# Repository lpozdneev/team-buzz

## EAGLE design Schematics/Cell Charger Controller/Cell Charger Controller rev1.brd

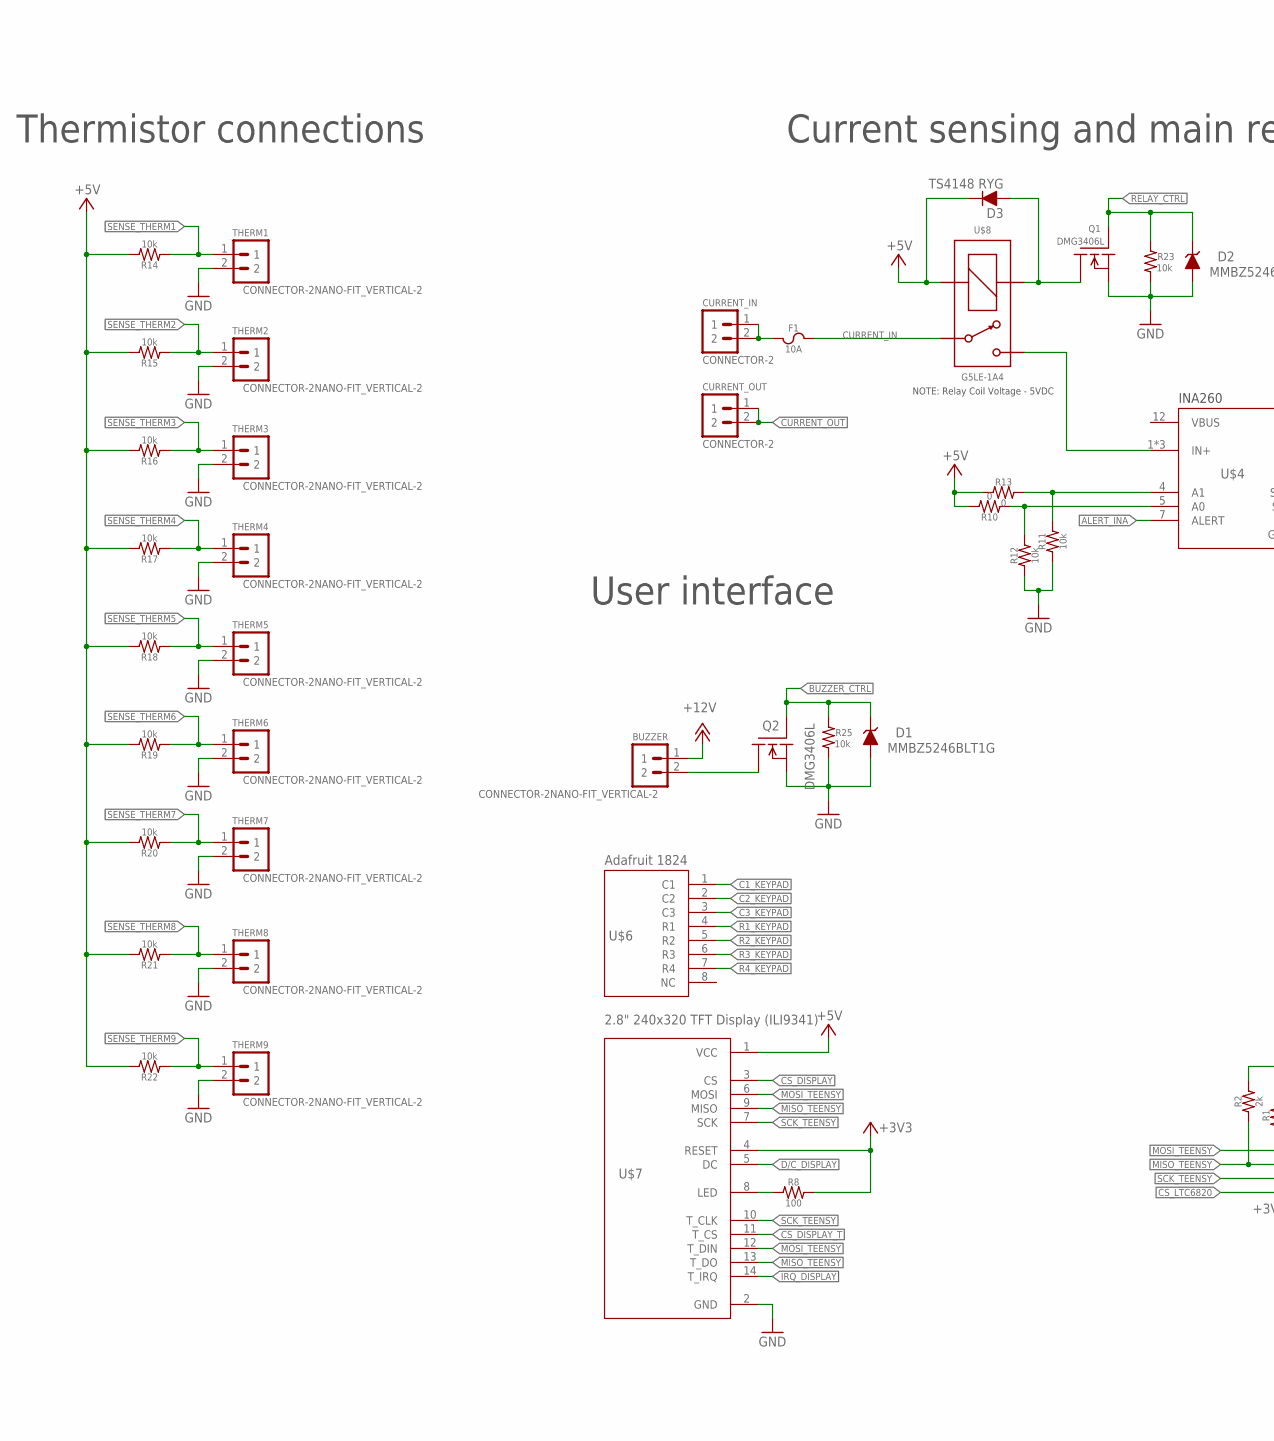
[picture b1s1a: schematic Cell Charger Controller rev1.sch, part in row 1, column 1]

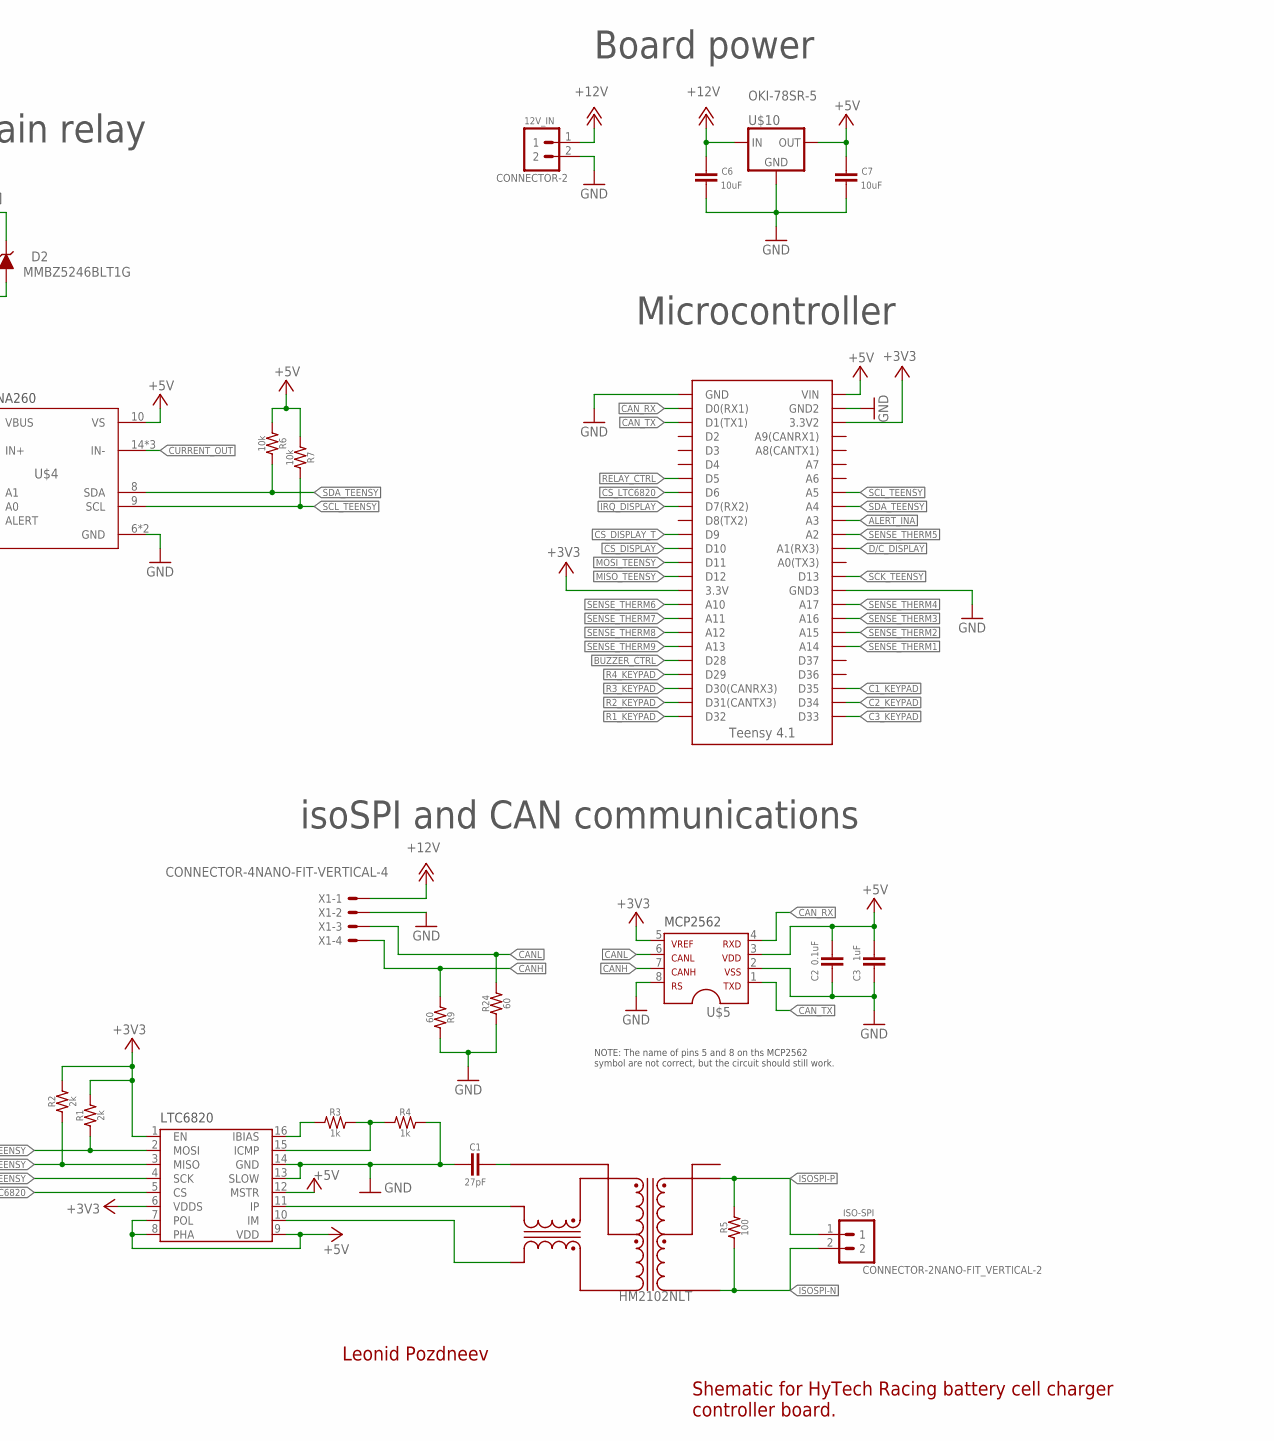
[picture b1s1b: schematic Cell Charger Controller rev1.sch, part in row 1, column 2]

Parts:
12V_IN: CONNECTOR-2; 39288020
BUZZER: CONNECTOR-2NANO-FIT_VERTICAL-2; 1053091202
C1: 27pF; 0603-CAP
C2: 0.1uF; 0603-CAP
C3: 1uF; 0603-CAP
C6, C7: 10uF; 0603-CAP
CURRENT_IN: CONNECTOR-2; 39288020
CURRENT_OUT: CONNECTOR-2; 39288020
D1, D2: MMBZ5246BLT1G; SOT23
D3: TS4148 RYG; 0805_D
F1: 10A; MINI-BLADE_FUSE_HOLDER
ISO-SPI: CONNECTOR-2NANO-FIT_VERTICAL-2; 1053091202
Q1, Q2: DMG3406L; SOT23
R1, R2: 2k; 0603-RES
R3, R4: 1k; 0603-RES
R5, R8: 100; 0603-RES
R6, R7, R11, R12, R14, R15, R16, R17, R18, R19, R20, R21, R22, R23, R25: 10k; 0603-RES
R9, R24: 60; 0603-RES
R10, R13: 0; 0603-RES
THERM1, THERM2, THERM3, THERM4, THERM5, THERM6, THERM7, THERM8, THERM9: CONNECTOR-2NANO-FIT_VERTICAL-2; 1053091202
U1: HM2102NLT
U$2: TEENSY_4.1_SIMPLE
U$3: LTC6820; MSOP-16
U$4: INA260; TSSOP-16
U$5: MCP2562FD; SOIC-08
U$6: ADAFRUIT_1824_KEYPAD
U$7: ILI9341_TOUCH_SCREEN
U$8: G5LE-1A4
U$10: OKI-78SR-5; OKI-78SR
X1: CONNECTOR-4NANO-FIT-VERTICAL-4; 1053101204

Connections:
+3V3: R1.2, R2.2, R8.2, U$2.3.3V, U$2.3.3V2, U$3.1 (EN), U$3.6 (VDDS), U$5.5, U$7.4 (RESET)
+5V: C2.1, C3.1, C7.1, D3.C, R6.1, R7.1, R10.2, R13.1, R14.2, R15.2, R16.2, R17.2, R18.2, R19.2, R20.2, R21.2, R22.2, U$2.VIN, U$3.7 (POL), U$3.8 (PHA), U$3.9 (VDD), U$3.12 (MSTR), U$4.10 (VS), U$5.3, U$7.1 (VCC), U$8.2 (COIL-), U$10.3 (OUT)
+12V: 12V_IN.1, BUZZER.1, C6.1, U$10.1 (IN), X1.1
ALERT_INA: U$2.A3, U$4.7 (ALERT)
BUZZER_CTRL: D1.3 (C), Q2.1 (G), R25.2, U$2.D28
C1_KEYPAD: U$2.D35, U$6.1 (C1)
C2_KEYPAD: U$2.D34, U$6.2 (C2)
C3_KEYPAD: U$2.D33, U$6.3 (C3)
CANH: R9.1, U$5.7, X1.4
CANL: R24.2, U$5.6, X1.3
CAN_RX: U$2.D0(RX1), U$5.4
CAN_TX: U$2.D1(TX1), U$5.1
CS_DISPLAY: U$2.D10, U$7.3 (CS)
CS_DISPLAY_T: U$2.D9, U$7.11 (T_CS)
CS_LTC6820: U$2.D6, U$3.5 (CS)
CURRENT_IN: F1.R1 (2), F1.R2 (2), U$8.P
CURRENT_OUT: CURRENT_OUT.1, CURRENT_OUT.2, U$4.14 (IN-), U$4.15 (IN-), U$4.16 (IN-)
D/C_DISPLAY: U$2.A1(RX3), U$7.5 (DC)
GND: 12V_IN.2, C1.2, C2.2, C3.2, C6.2, C7.2, D1.1 (A), D2.1 (A), Q1.2 (S), Q2.2 (S), R4.2, R9.2, R11.1, R12.1, R23.1, R24.1, R25.1, THERM1.2, THERM2.2, THERM3.2, THERM4.2, THERM5.2, THERM6.2, THERM7.2, THERM8.2, THERM9.2, U$2.GND, U$2.GND2, U$2.GND3, U$3.13 (SLOW), U$3.14 (GND), U$4.6 (GND), U$4.11 (GND), U$5.2, U$5.8, U$7.2 (GND), U$10.2 (GND), X1.2
IRQ_DISPLAY: U$2.D7(RX2), U$7.14 (T_IRQ)
ISOSPI-N: ISO-SPI.2, R5.1, U1.P$3 (MX-)
ISOSPI-P: ISO-SPI.1, R5.2, U1.P$1 (MX+)
MISO_TEENSY: R2.1, U$2.D12, U$3.3 (MISO), U$7.9 (MISO), U$7.13 (T_DO)
MOSI_TEENSY: R1.1, U$2.D11, U$3.2 (MOSI), U$7.6 (MOSI), U$7.12 (T_DIN)
unnamed: C1.1, U1.P$11 (TCT)
unnamed: U1.P$12 (TD+), U$3.11 (IP)
unnamed: U1.P$10 (TD-), U$3.10 (IM)
unnamed: R3.1, U$3.16 (IBIAS)
unnamed: R3.2, R4.1, U$3.15 (ICMP)
unnamed: R11.2, R13.2, U$4.4 (A1)
unnamed: R10.1, R12.2, U$4.5 (A0)
unnamed: R8.1, U$7.8 (LED)
unnamed: CURRENT_IN.1, CURRENT_IN.2, F1.L1 (1), F1.L2 (1)
unnamed: U$4.1 (IN+), U$4.2 (IN+), U$4.3 (IN+), U$8.S
unnamed: D3.A, Q1.3 (D), U$8.1 (COIL+)
unnamed: BUZZER.2, Q2.3 (D)
R1_KEYPAD: U$2.D32, U$6.4 (R1)
R2_KEYPAD: U$2.D31(CANTX) (D31(CANTX3)), U$6.5 (R2)
R3_KEYPAD: U$2.D30(CANRX) (D30(CANRX3)), U$6.6 (R3)
R4_KEYPAD: U$2.D29, U$6.7 (R4)
RELAY_CTRL: D2.3 (C), Q1.1 (G), R23.2, U$2.D5
SCK_TEENSY: U$2.D13, U$3.4 (SCK), U$7.7 (SCK), U$7.10 (T_CLK)
SCL_TEENSY: R7.2, U$2.A5, U$4.9 (SCL)
SDA_TEENSY: R6.2, U$2.A4, U$4.8 (SDA)
SENSE_THERM1: R14.1, THERM1.1, U$2.A14
SENSE_THERM2: R15.1, THERM2.1, U$2.A15
SENSE_THERM3: R16.1, THERM3.1, U$2.A16
SENSE_THERM4: R17.1, THERM4.1, U$2.A17
SENSE_THERM5: R18.1, THERM5.1, U$2.A2
SENSE_THERM6: R19.1, THERM6.1, U$2.A10
SENSE_THERM7: R20.1, THERM7.1, U$2.A11
SENSE_THERM8: R21.1, THERM8.1, U$2.A12
SENSE_THERM9: R22.1, THERM9.1, U$2.A13

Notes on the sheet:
NOTE: The name of pins 5 and 8 on ths MCP2562 symbol are not correct, but the circuit should still work.
INA260
MCP2562
LTC6820
NOTE: Relay Coil Voltage - 5VDC
Leonid Pozdneev
Shematic for HyTech Racing battery cell charger controller board.
User interface
Thermistor connections
Current sensing and main relay
Microcontroller
isoSPI and CAN communications
Board power

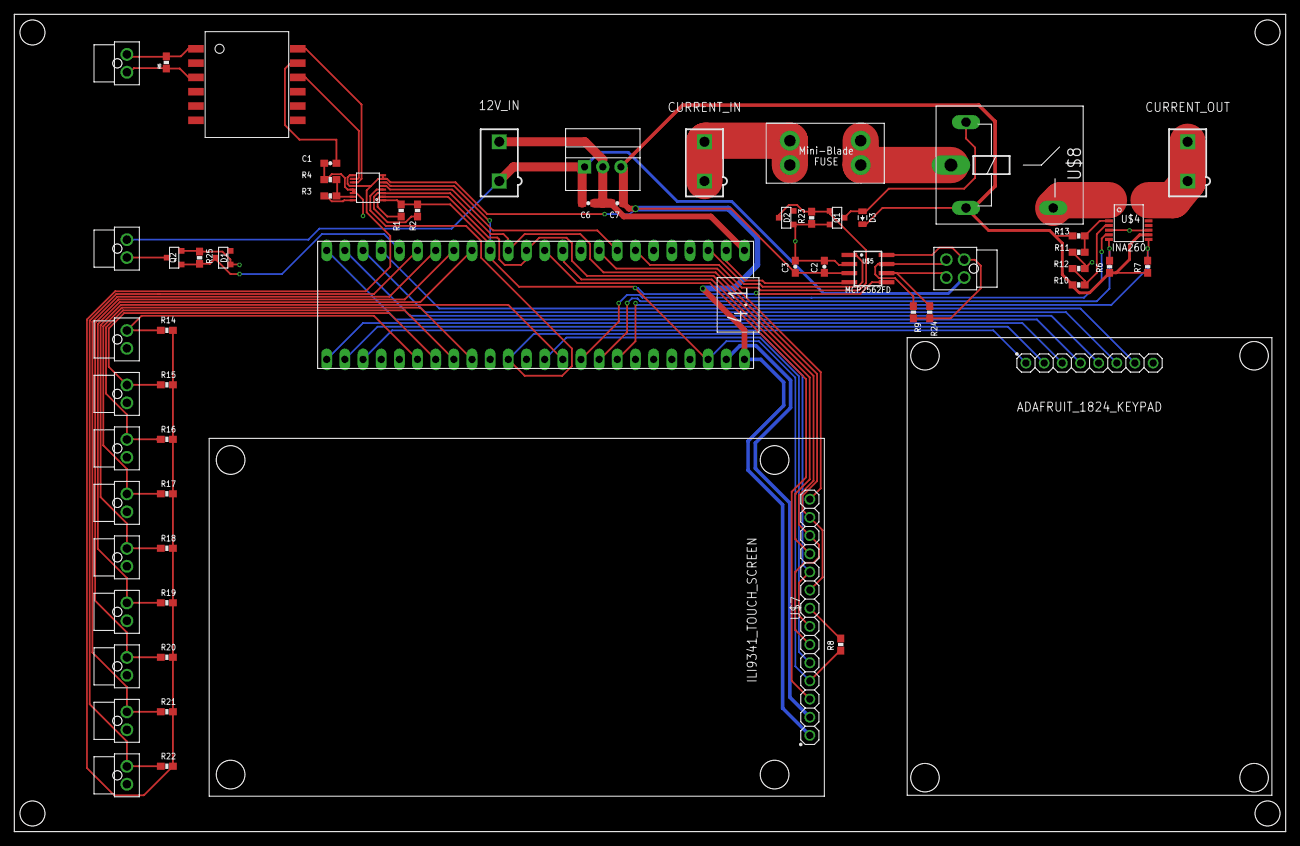
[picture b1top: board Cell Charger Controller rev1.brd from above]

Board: 2 copper layers, 177.8 x 114.3 mm, 60 parts (0 on the bottom side), 53 nets.

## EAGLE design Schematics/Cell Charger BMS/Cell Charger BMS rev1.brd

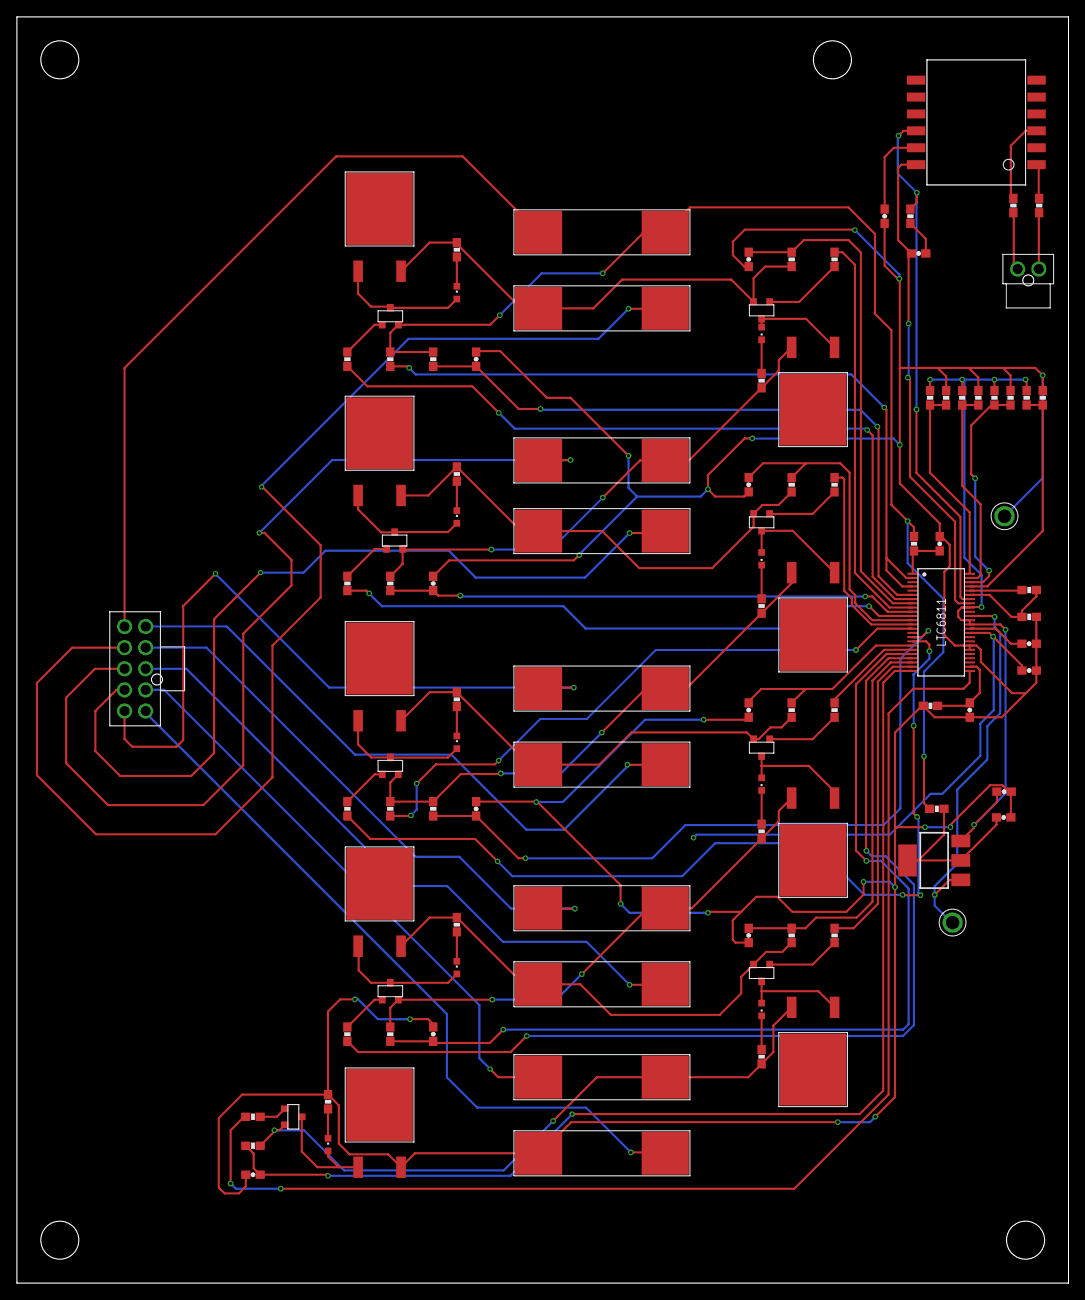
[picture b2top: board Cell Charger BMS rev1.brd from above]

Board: 2 copper layers, 124.5 x 149.9 mm, 110 parts (0 on the bottom side), 88 nets.

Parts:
C1_B, C2_B, C8_B: 1uF; 0603-CAP
C3_B: 15pF; 0603-CAP
C4_B: 10nF; 0603-CAP
C6_B, C7_B: 100nF; 0603-CAP
C_5: 10nF; 0603-CAP
DRAIN1:C, DRAIN2:C, DRAIN3:C, DRAIN4:C, DRAIN5:C, DRAIN6:C, DRAIN7:C, DRAIN8:C, DRAIN9:C: 10nF; 0603-CAP
DRAIN1:DISCHARGE, DRAIN2:DISCHARGE, DRAIN3:DISCHARGE, DRAIN4:DISCHARGE, DRAIN5:DISCHARGE, DRAIN6:DISCHARGE, DRAIN7:DISCHARGE, DRAIN8:DISCHARGE, DRAIN9:DISCHARGE: 5R; PWR163
DRAIN1:GATE, DRAIN2:GATE, DRAIN3:GATE, DRAIN4:GATE, DRAIN5:GATE, DRAIN6:GATE, DRAIN7:GATE, DRAIN8:GATE, DRAIN9:GATE: 3K3; 0603-RES
DRAIN1:LED1, DRAIN2:LED1, DRAIN3:LED1, DRAIN4:LED1, DRAIN5:LED1, DRAIN6:LED1, DRAIN7:LED1, DRAIN8:LED1, DRAIN9:LED1: RED; LED-603
DRAIN1:PFET, DRAIN2:PFET, DRAIN3:PFET, DRAIN4:PFET, DRAIN5:PFET, DRAIN6:PFET, DRAIN7:PFET, DRAIN8:PFET, DRAIN9:PFET: P-CHANNEL_MOSFET_DMP3099L-7; SOT23
DRAIN1:R, DRAIN2:R, DRAIN3:R, DRAIN4:R, DRAIN5:R, DRAIN6:R, DRAIN7:R, DRAIN8:R, DRAIN9:R: 100R; 0603-RES
DRAIN1:R1, DRAIN2:R1, DRAIN3:R1, DRAIN4:R1, DRAIN5:R1, DRAIN6:R1, DRAIN7:R1, DRAIN8:R1, DRAIN9:R1: 806R; 0603-RES
F0, F1, F2, F3, F4, F5, F6, F7, F8, F9: 0001.2704.11; 5X20MM_FUSE
J1_B, J2_B, J3_B, J4_B, J5_B, J6_B, J7_B, J8_B: 0R; 0603-RES
Q2: NSV1C201MZ4; SOT223
R1_B, R2_B: 100R; 0603-RES
R3_B: 402R; 0603-RES
R4_B, R5_B: 22R; 0603-RES
RB1_B: 1K2; 0603-RES
RB2_B: 806R; 0603-RES
RIN_B: 100R; 0603-RES
RU1_B, RU2_B: 100R; 0603-RES
TRANSFORMER: HM2102NLT
U2: LTC6811-2; LTC6811
U$6, U$7: TEST_POINT
U$13, U$14, U$16, U$27: M4_MOUNTING
X1: CONNECTOR-10NANO-FIT_VERTICAL-10; 1053101210
X2: CONNECTOR-2NANO-FIT_VERTICAL-2; 1053091202

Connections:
C0_B: C_5.1, R2_B.2, U2.26
C1_B: DRAIN1:C.1, DRAIN1:R.2, U2.24
C2_B: DRAIN2:C.1, DRAIN2:R.2, U2.22
C3_B: DRAIN3:C.1, DRAIN3:R.2, U2.20
C4_B: DRAIN4:C.1, DRAIN4:R.2, U2.18
C5_B: DRAIN5:C.1, DRAIN5:R.2, U2.16
C7_B: DRAIN6:C.1, DRAIN6:R.2, U2.12
C8_B: DRAIN7:C.1, DRAIN7:R.2, U2.10
C9_B: DRAIN8:C.1, DRAIN8:R.2, U2.8
C10_B: DRAIN9:C.1, DRAIN9:R.2, U2.6
CC0: F0.P$1, X1.P$1
CC1: F1.P$1, X1.P$2
CC2: F2.P$1, X1.P$3
CC3: F3.P$1, X1.P$4
CC4: F4.P$1, X1.P$5
CC5: F5.P$1, X1.P$6
CC6: F6.P$1, X1.P$7
CC7: F7.P$1, X1.P$8
CC8: F8.P$1, X1.P$9
DRAIN1:GATE: DRAIN1:GATE.1, DRAIN1:PFET.1
DRAIN1:N$1: DRAIN1:DISCHARGE.1, DRAIN1:LED1.A, DRAIN1:PFET.3
DRAIN1:N$2: DRAIN1:LED1.C, DRAIN1:R1.2
DRAIN2:GATE: DRAIN2:GATE.1, DRAIN2:PFET.1
DRAIN2:N$1: DRAIN2:DISCHARGE.1, DRAIN2:LED1.A, DRAIN2:PFET.3
DRAIN2:N$2: DRAIN2:LED1.C, DRAIN2:R1.2
DRAIN3:GATE: DRAIN3:GATE.1, DRAIN3:PFET.1
DRAIN3:N$1: DRAIN3:DISCHARGE.1, DRAIN3:LED1.A, DRAIN3:PFET.3
DRAIN3:N$2: DRAIN3:LED1.C, DRAIN3:R1.2
DRAIN4:GATE: DRAIN4:GATE.1, DRAIN4:PFET.1
DRAIN4:N$1: DRAIN4:DISCHARGE.1, DRAIN4:LED1.A, DRAIN4:PFET.3
DRAIN4:N$2: DRAIN4:LED1.C, DRAIN4:R1.2
DRAIN5:GATE: DRAIN5:GATE.1, DRAIN5:PFET.1
DRAIN5:N$1: DRAIN5:DISCHARGE.1, DRAIN5:LED1.A, DRAIN5:PFET.3
DRAIN5:N$2: DRAIN5:LED1.C, DRAIN5:R1.2
DRAIN6:GATE: DRAIN6:GATE.1, DRAIN6:PFET.1
DRAIN6:N$1: DRAIN6:DISCHARGE.1, DRAIN6:LED1.A, DRAIN6:PFET.3
DRAIN6:N$2: DRAIN6:LED1.C, DRAIN6:R1.2
DRAIN7:GATE: DRAIN7:GATE.1, DRAIN7:PFET.1
DRAIN7:N$1: DRAIN7:DISCHARGE.1, DRAIN7:LED1.A, DRAIN7:PFET.3
DRAIN7:N$2: DRAIN7:LED1.C, DRAIN7:R1.2
DRAIN8:GATE: DRAIN8:GATE.1, DRAIN8:PFET.1
DRAIN8:N$1: DRAIN8:DISCHARGE.1, DRAIN8:LED1.A, DRAIN8:PFET.3
DRAIN8:N$2: DRAIN8:LED1.C, DRAIN8:R1.2
DRAIN9:GATE: DRAIN9:GATE.1, DRAIN9:PFET.1
DRAIN9:N$1: DRAIN9:DISCHARGE.1, DRAIN9:LED1.A, DRAIN9:PFET.3
DRAIN9:N$2: DRAIN9:LED1.C, DRAIN9:R1.2
DRIVE_B: Q2.1, U2.38, U$7.P$1
IM_B: C3_B.2, TRANSFORMER.P$12, U2.41
IP_B: R3_B.1, TRANSFORMER.P$10, U2.42
ISOSPI-M: R5_B.2, X2.2
ISOSPI-P: R4_B.2, X2.1
unnamed: C4_B.1, TRANSFORMER.P$11
unnamed: RB1_B.2, U2.44
unnamed: F9.P$1, X1.P$10
unnamed: RB1_B.1, RB2_B.2, U2.43
unnamed: R4_B.1, TRANSFORMER.P$3
unnamed: R5_B.1, TRANSFORMER.P$1
unnamed: J7_B.1, J8_B.1, U2.48
unnamed: J5_B.1, J6_B.1, U2.47
unnamed: C3_B.1, R3_B.2
unnamed: J3_B.1, J4_B.1, U2.46
unnamed: J1_B.1, J2_B.1, U2.45
S1_B: DRAIN1:GATE.2, U2.25
S2_B: DRAIN2:GATE.2, U2.23
S3_B: DRAIN3:GATE.2, U2.21
S4_B: DRAIN4:GATE.2, U2.19
S5_B: DRAIN5:GATE.2, U2.17
S7_B: DRAIN6:GATE.2, U2.13
S8_B: DRAIN7:GATE.2, U2.11
S9_B: DRAIN8:GATE.2, U2.9
S10_B: DRAIN9:GATE.2, U2.7
SENSE1: DRAIN1:PFET.2, DRAIN1:R.1, DRAIN2:DISCHARGE.2, DRAIN2:R1.1, F1.P$2
SENSE2: DRAIN2:PFET.2, DRAIN2:R.1, DRAIN3:DISCHARGE.2, DRAIN3:R1.1, F2.P$2
SENSE3: DRAIN3:PFET.2, DRAIN3:R.1, DRAIN4:DISCHARGE.2, DRAIN4:R1.1, F3.P$2
SENSE4: DRAIN4:PFET.2, DRAIN4:R.1, DRAIN5:DISCHARGE.2, DRAIN5:R1.1, F4.P$2
SENSE5: DRAIN5:PFET.2, DRAIN5:R.1, DRAIN6:DISCHARGE.2, DRAIN6:R1.1, F5.P$2, RU2_B.1
SENSE6: DRAIN6:PFET.2, DRAIN6:R.1, DRAIN7:DISCHARGE.2, DRAIN7:R1.1, F6.P$2
SENSE7: DRAIN7:PFET.2, DRAIN7:R.1, DRAIN8:DISCHARGE.2, DRAIN8:R1.1, F7.P$2
SENSE8: DRAIN8:PFET.2, DRAIN8:R.1, DRAIN9:DISCHARGE.2, DRAIN9:R1.1, F8.P$2
UNUSED1_B: RU1_B.2, U2.2, U2.4
UNUSED2_B: RU2_B.2, U2.14
V+_B: C6_B.1, R1_B.2, U2.1
V-_A: DRAIN9:PFET.2, DRAIN9:R.1, F9.P$2, R1_B.1, RIN_B.1, RU1_B.1
V-_B: C1_B.2, C2_B.2, C4_B.2, C6_B.2, C7_B.2, C8_B.2, C_5.2, DRAIN1:C.2, DRAIN1:DISCHARGE.2, DRAIN1:R1.1, DRAIN2:C.2, DRAIN3:C.2, DRAIN4:C.2, DRAIN5:C.2, DRAIN6:C.2, DRAIN7:C.2, DRAIN8:C.2, DRAIN9:C.2, F0.P$2, J1_B.2, J3_B.2, J5_B.2, J7_B.2, R2_B.1, RB2_B.1, U2.30, U2.31, U$6.P$1
VIN_B: C7_B.1, Q2.2, Q2.4, RIN_B.2
VREF1_B: C2_B.1, U2.35
VREF2_B: C1_B.1, U2.34
VREG_B: C8_B.1, J2_B.2, J4_B.2, J6_B.2, J8_B.2, Q2.3, U2.36, U2.37, U2.40

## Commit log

2021-02-03 added HyTech BMS schematics
2021-02-03 added relevant HyTech code and libraries
2021-02-03 inital commit for battery analysis
2021-02-03 added HyTech HV control board schematics
2021-02-03 got an inital plot going
2021-02-05 first draft of the full system diagram
2021-03-03 added current sensor into the system diagram and added some schematic pictures
2021-03-20 controller board WiP
2021-03-20 added HyTech Eagle libraries
2021-03-22 board almost done
2021-03-23 charger controller board ready for review
2021-03-23 charger BMS WiP
2021-03-23 charger BMS almost done
2021-03-29 small changes to the controller board
2021-03-29 generated gerbers for charger controller
2021-03-31 moved old code into seperate folder and added tenmplate for state machine
2021-04-12 website stuff
2021-04-20 Keypad Code
2021-04-21 Current Sensor Demo
2021-04-27 updates to website and organized code
